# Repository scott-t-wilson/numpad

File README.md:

# numpad
DIY USB numpad - C++ code for teensy + schematic and pcb

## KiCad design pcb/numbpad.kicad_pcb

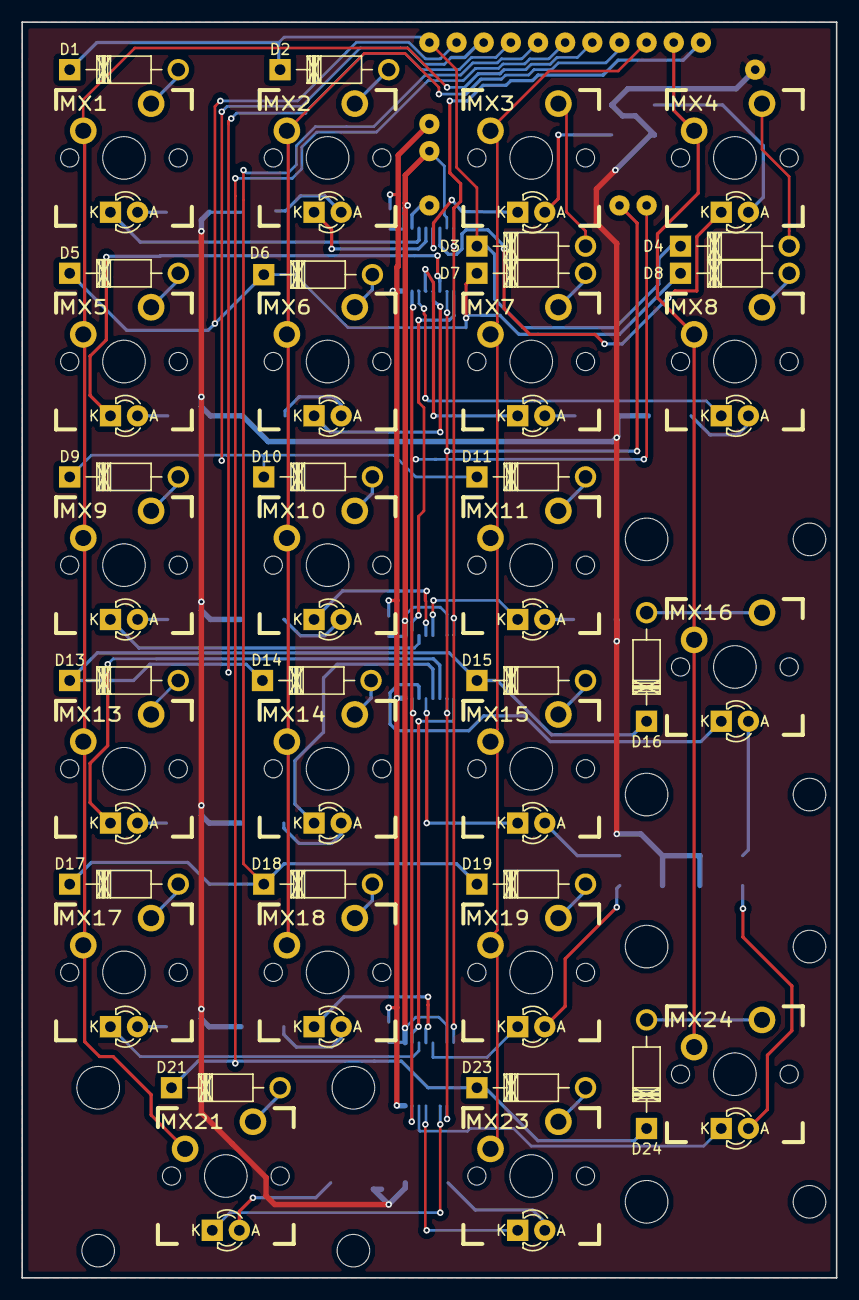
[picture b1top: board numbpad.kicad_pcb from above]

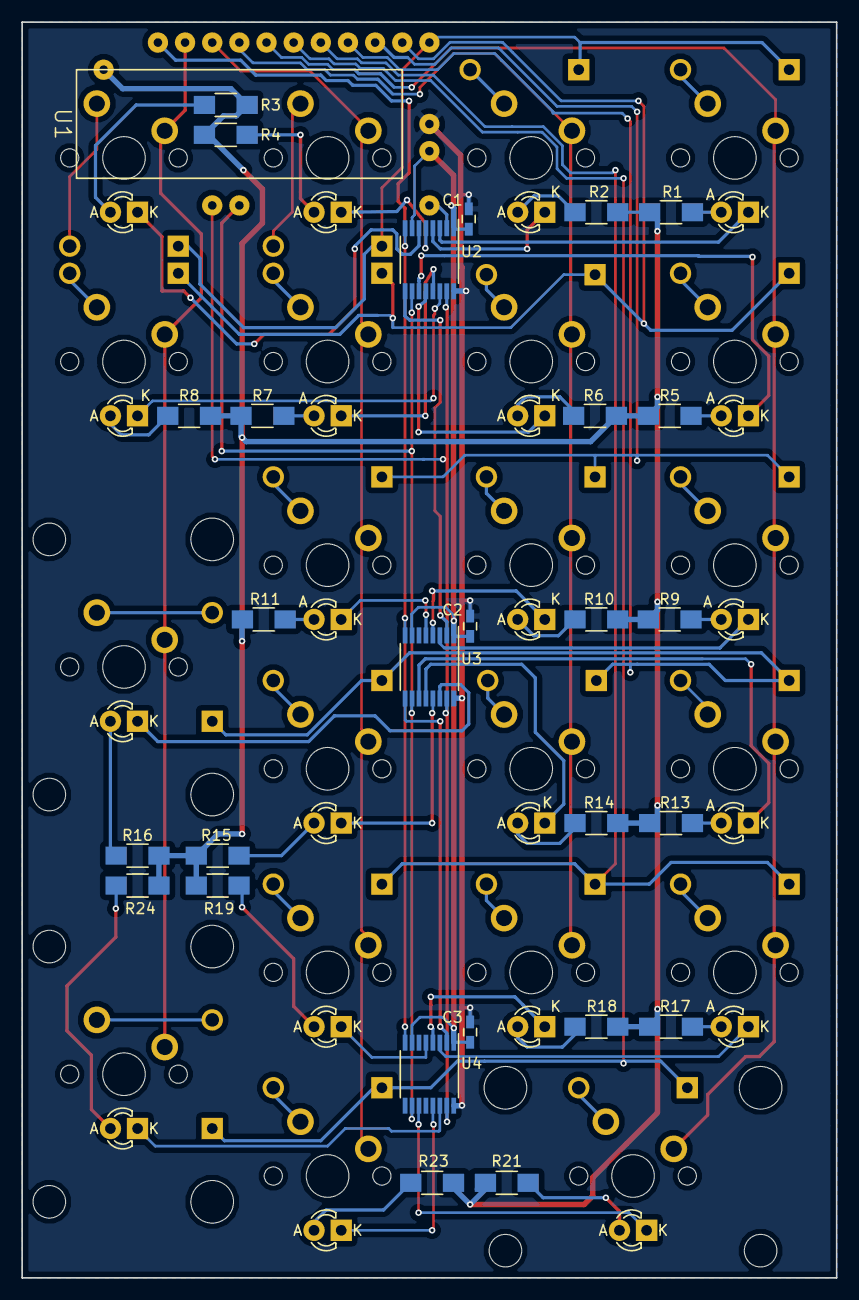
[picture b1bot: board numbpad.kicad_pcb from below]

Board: 2 copper layers, 76.2 x 117.5 mm, 73 parts (28 on the bottom side), 82 nets.

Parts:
C1, C2, C3: C; C_0603_HandSoldering
D1, D2, D3, D4, D5, D6, D7, D8, D9, D10, D11, D13, D14, D15, D16, D17, D18, D19, D21, D23, D24: D; Diode_DO-41_SOD81_Horizontal_RM10
MX1, MX2, MX3, MX4, MX5, MX6, MX7, MX8, MX9, MX10, MX11, MX13, MX14, MX15, MX16, MX17, MX18, MX19, MX21, MX23, MX24: MX; CHERRY_PCB_100H_LED
R1, R2, R3, R4, R5, R6, R7, R8, R9, R10, R11, R13, R14, R15, R16, R17, R18, R19, R21, R23, R24: R; R_1206_HandSoldering
STA: Stabilizer; CHERRY_PCB_200_STABILIZER
STA#2, STA#3: Stabilizer; CHERRY_PCB_200_STABILIZER
U1: Teensy_3.2_Partial_small; Teensy-3.2-partial-small
U2, U3, U4: TLC6C598; TSSOP-16_4.4x5mm_Pitch0.65mm

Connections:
+3V3: C1.1, C2.1, C3.1, U1.3v3, U2.1, U2.7, U3.1, U3.7, U4.1, U4.7
+5V: R1.1, R2.1, R3.1, R4.1, R5.1, R6.1, R7.1, R8.1, R9.1, R10.1, R11.1, R13.1, R14.1, R15.1, R16.1, R17.1, R18.1, R19.1, R21.1, R23.1, R24.1, U1.VUSB
Col1: MX1.SW1, MX5.SW1, MX9.SW1, MX13.SW1, MX17.SW1, MX21.SW1, U1.19
Col2: MX2.SW1, MX6.SW1, MX10.SW1, MX14.SW1, MX18.SW1, U1.20
Col3: MX3.SW1, MX7.SW1, MX11.SW1, MX15.SW1, MX19.SW1, MX23.SW1, U1.21
Col4: MX4.SW1, MX8.SW1, MX16.SW1, MX24.SW1, U1.22
GND: C1.2, C2.2, C3.2, U1.GND1, U2.16, U3.16, U4.16
unnamed: D1.2, MX1.SW2
unnamed: D2.2, MX2.SW2
unnamed: D3.2, MX3.SW2
unnamed: D4.2, MX4.SW2
unnamed: D5.2, MX5.SW2
unnamed: D6.2, MX6.SW2
unnamed: D7.2, MX7.SW2
unnamed: D8.2, MX8.SW2
unnamed: D9.2, MX9.SW2
unnamed: D10.2, MX10.SW2
unnamed: D11.2, MX11.SW2
unnamed: D13.2, MX13.SW2
unnamed: D14.2, MX14.SW2
unnamed: D15.2, MX15.SW2
unnamed: D16.2, MX16.SW2
unnamed: D17.2, MX17.SW2
unnamed: D18.2, MX18.SW2
unnamed: D19.2, MX19.SW2
unnamed: D21.2, MX21.SW2
unnamed: D23.2, MX23.SW2
unnamed: D24.2, MX24.SW2
unnamed: MX1.A, R1.2
unnamed: MX1.K, U2.3
unnamed: MX2.A, R2.2
unnamed: MX2.K, U2.4
unnamed: MX3.A, R3.2
unnamed: MX3.K, U2.5
unnamed: MX4.A, R4.2
unnamed: MX4.K, U2.6
unnamed: MX5.A, R5.2
unnamed: MX5.K, U2.11
unnamed: MX6.A, R6.2
unnamed: MX6.K, U2.12
unnamed: MX7.A, R7.2
unnamed: MX7.K, U2.13
unnamed: MX8.A, R8.2
unnamed: MX8.K, U2.14
unnamed: MX9.A, R9.2
unnamed: MX9.K, U3.3
unnamed: MX10.A, R10.2
unnamed: MX10.K, U3.4
unnamed: MX11.A, R11.2
unnamed: MX11.K, U3.5
unnamed: MX13.A, R13.2
unnamed: MX13.K, U3.11
unnamed: MX14.A, R14.2
unnamed: MX14.K, U3.12
unnamed: MX15.A, R15.2
unnamed: MX15.K, U3.13
unnamed: MX16.A, R16.2
unnamed: MX16.K, U3.14
unnamed: MX17.A, R17.2
unnamed: MX17.K, U4.3
unnamed: MX18.A, R18.2
unnamed: MX18.K, U4.4
unnamed: MX19.A, R19.2
unnamed: MX19.K, U4.5
unnamed: MX21.A, R21.2
unnamed: MX21.K, U4.11
unnamed: MX23.A, R23.2
unnamed: MX23.K, U4.13
unnamed: MX24.A, R24.2
unnamed: MX24.K, U4.14
unnamed: U2.9, U3.2
unnamed: U3.9, U4.2
PWM: U1.23, U2.8, U3.8, U4.8
RCLK: U1.5, U2.10, U3.10, U4.10
Row1: D1.1, D2.1, D3.1, D4.1, U1.13
Row2: D5.1, D6.1, D7.1, D8.1, U1.14
Row3: D9.1, D10.1, D11.1, U1.15
Row4: D13.1, D14.1, D15.1, D16.1, U1.16
Row5: D17.1, D18.1, D19.1, U1.17
Row6: D21.1, D23.1, D24.1, U1.18
SCLK: U1.4, U2.15, U3.15, U4.15
SER: U1.12, U2.2

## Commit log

2016-04-09 Remove older teensy 3 support
2016-04-09 Add kicad backups to ignore
2016-04-09 Added files that were used to make the Rev1 order. These are known working- successul numbpad has been built from these gerbers.
